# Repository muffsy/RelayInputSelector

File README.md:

# Muffsy Relay Input Selector 4

This open source (BSD license) project contains Arduino Code, Autodesk Eagle PCB project files and gerbers that can be sent directly to any PCB manufacturer for production.

- https://www.muffsy.com/muffsy-relay-input-selector-4.html
- https://www.tindie.com/products/skrodahl/muffsy-relay-input-selector-kit/

The Muffsy Relay Input Selector is a simple, reliable, high quality, DIY stereo input selector that's controlled by an ESP-32 and is slightly larger than a Post-IT note. 

The Input Selector has four inputs, one output, a mute circuit and the option of controlling a solid state relay. It's controlled with a rotary encoder and an IR remote. 

As the heart of the Input Selector is an ESP32, with all pins broken out on the board, the possibilities are virtually limitles. The example code is written in Arduino, the native SDK could of course be used instead.

This kit is meant to be paired with a preamplifier circuit, such as the Muffsy BSTRD Class-A Tube Preamp, Pass Labs B1 and many others.

**This project**, including the schematic and board layout, **is open source**. It's licensed under the very permissive BSD 3-Clause "New" or "Revised" License.

**Update 2023-07-30:**
The software now works without modifications of Arduino libraries.

**Update 2023-09-16:**
Much improved code, with user configurable values. In particular for the IR remote codes and rotary encoder direction.

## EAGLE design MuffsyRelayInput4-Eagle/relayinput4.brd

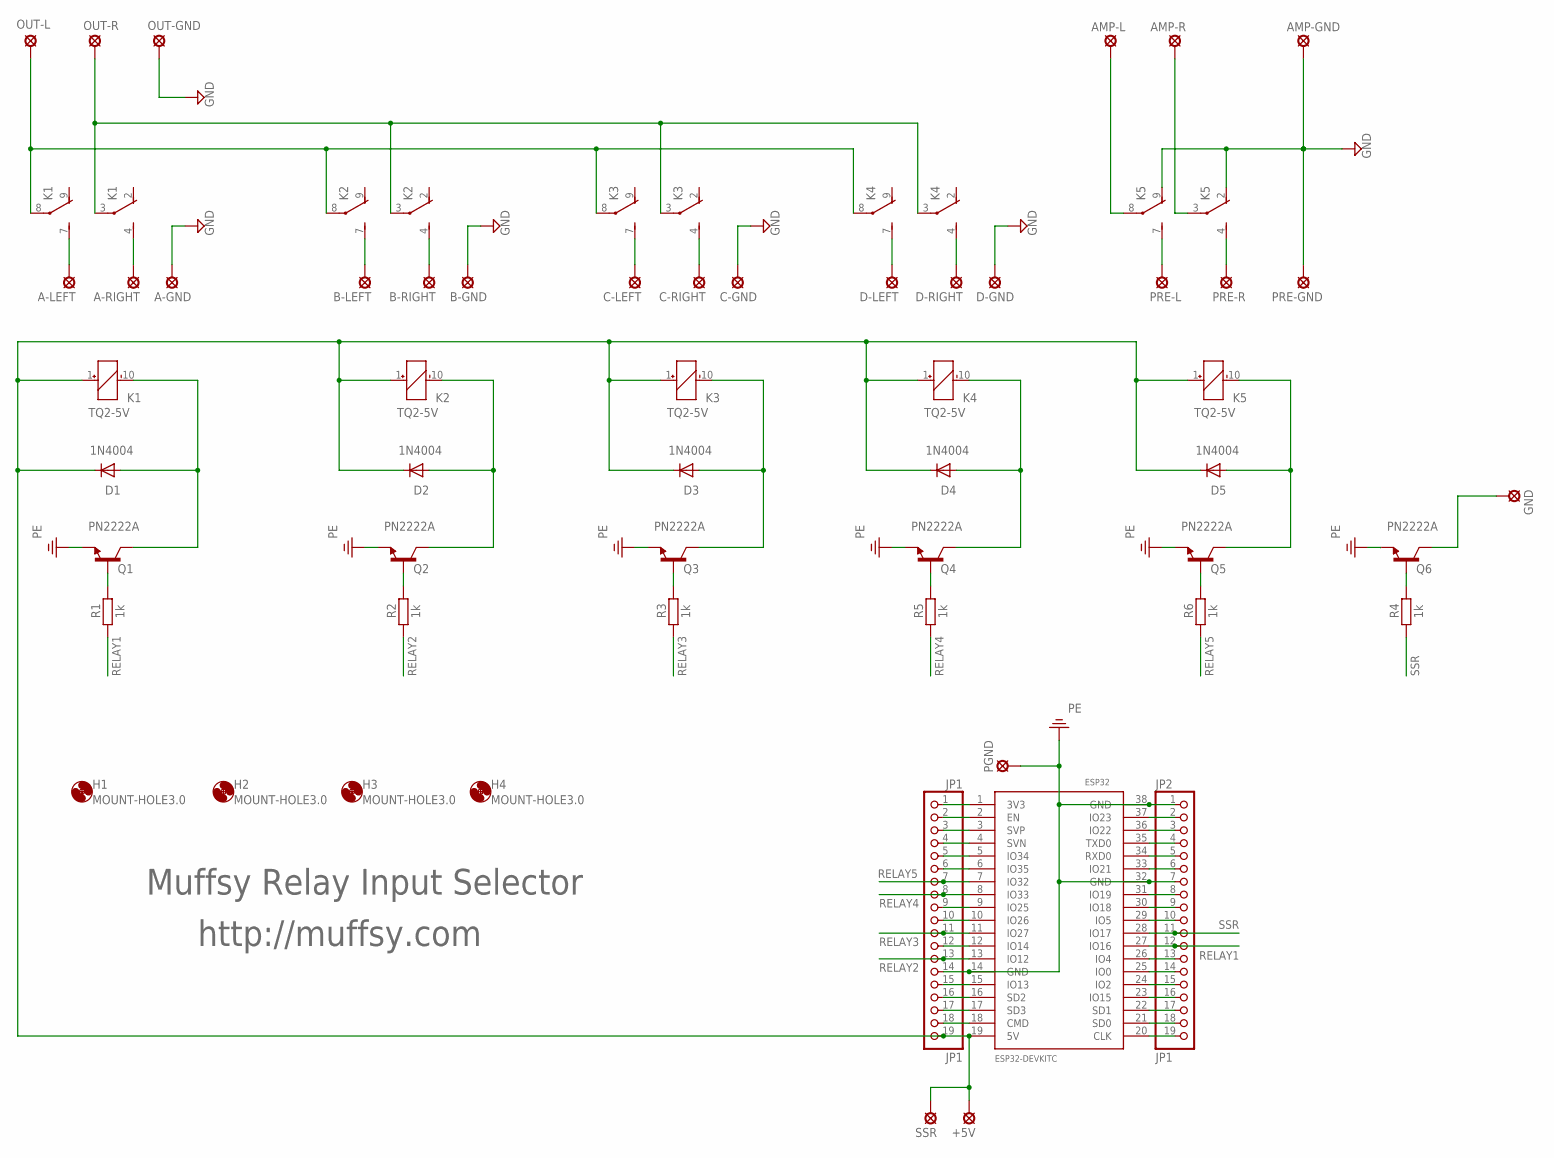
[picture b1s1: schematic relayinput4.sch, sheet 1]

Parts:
+5V: SE11
A-GND: SE11
A-LEFT: SE11
A-RIGHT: SE11
AMP-GND: SE11
AMP-L: SE11
AMP-R: SE11
B-GND: SE11
B-LEFT: SE11
B-RIGHT: SE11
C-GND: SE11
C-LEFT: SE11
C-RIGHT: SE11
D1, D2, D3, D4, D5: 1N4004; DO41-10
D-GND: SE11
D-LEFT: SE11
D-RIGHT: SE11
ESP32: ESP32DEVKITC; ESP32-DEVKITC
GND: SE11
H1, H2, H3, H4: MOUNT-HOLE3.0; 3,0
JP1, JP2: JP1; 1X19
K1, K2, K3, K4, K5: TQ2-5V; TQ2
OUT-GND: SE11
OUT-L: SE11
OUT-R: SE11
PGND: SE11
PRE-GND: SE11
PRE-L: SE11
PRE-R: SE11
Q1, Q2, Q3, Q4, Q5, Q6: PN2222A; TO92
R1, R2, R3, R4, R5, R6: 1k; 0207/10
SSR: SE11

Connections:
GND: A-GND.MP, AMP-GND.MP, B-GND.MP, C-GND.MP, D-GND.MP, K5.2 (O), K5.9 (O), OUT-GND.MP, PRE-GND.MP
unnamed: B-LEFT.MP, K2.7 (S)
unnamed: A-LEFT.MP, K1.7 (S)
unnamed: A-RIGHT.MP, K1.4 (S)
unnamed: B-RIGHT.MP, K2.4 (S)
unnamed: C-LEFT.MP, K3.7 (S)
unnamed: C-RIGHT.MP, K3.4 (S)
unnamed: D-LEFT.MP, K4.7 (S)
unnamed: D-RIGHT.MP, K4.4 (S)
unnamed: K5.7 (S), PRE-L.MP
unnamed: K5.4 (S), PRE-R.MP
unnamed: Q1.B, R1.2
unnamed: K1.3, K2.3, K3.3, K4.3, OUT-R.MP
unnamed: K1.8, K2.8, K3.8, K4.8, OUT-L.MP
unnamed: Q2.B, R2.2
unnamed: +5V.MP, D1.C, D2.C, D3.C, D4.C, D5.C, ESP32.19 (5V), JP1.19, K1.1 (+), K2.1 (+), K3.1 (+), K4.1 (+), K5.1 (+), SSR.MP
unnamed: Q3.B, R3.2
unnamed: Q4.B, R5.2
unnamed: Q5.B, R6.2
unnamed: ESP32.1 (3V3), JP1.1
unnamed: D1.A, K1.10 (-), Q1.C
unnamed: D2.A, K2.10 (-), Q2.C
unnamed: D3.A, K3.10 (-), Q3.C
unnamed: D4.A, K4.10 (-), Q4.C
unnamed: D5.A, K5.10 (-), Q5.C
unnamed: ESP32.2 (EN), JP1.2
unnamed: ESP32.3 (SVP), JP1.3
unnamed: ESP32.4 (SVN), JP1.4
unnamed: ESP32.5 (IO34), JP1.5
unnamed: ESP32.6 (IO35), JP1.6
unnamed: AMP-R.MP, K5.3
unnamed: AMP-L.MP, K5.8
unnamed: ESP32.10 (IO26), JP1.10
unnamed: ESP32.12 (IO14), JP1.12
unnamed: ESP32.9 (IO25), JP1.9
unnamed: GND.MP, Q6.C
unnamed: ESP32.15 (IO13), JP1.15
unnamed: Q6.B, R4.2
unnamed: ESP32.29 (IO5), JP2.10
unnamed: ESP32.36 (IO22), JP2.3
unnamed: ESP32.16 (SD2), JP1.16
unnamed: ESP32.17 (SD3), JP1.17
unnamed: ESP32.18 (CMD), JP1.18
unnamed: ESP32.37 (IO23), JP2.2
unnamed: ESP32.35 (TXD0), JP2.4
unnamed: ESP32.34 (RXD0), JP2.5
unnamed: ESP32.33 (IO21), JP2.6
unnamed: ESP32.31 (IO19), JP2.8
unnamed: ESP32.30 (IO18), JP2.9
unnamed: ESP32.26 (IO4), JP2.13
unnamed: ESP32.25 (IO0), JP2.14
unnamed: ESP32.24 (IO2), JP2.15
unnamed: ESP32.23 (IO15), JP2.16
unnamed: ESP32.22 (SD1), JP2.17
unnamed: ESP32.21 (SD0), JP2.18
unnamed: ESP32.20 (CLK), JP2.19
PE: ESP32.14 (GND), ESP32.32 (GND), ESP32.38 (GND), JP1.14, JP2.1, JP2.7, PGND.MP, Q1.E, Q2.E, Q3.E, Q4.E, Q5.E, Q6.E
RELAY1: ESP32.27 (IO16), JP2.12, R1.1
RELAY2: ESP32.13 (IO12), JP1.13, R2.1
RELAY3: ESP32.11 (IO27), JP1.11, R3.1
RELAY4: ESP32.8 (IO33), JP1.8, R5.1
RELAY5: ESP32.7 (IO32), JP1.7, R6.1
SSR: ESP32.28 (IO17), JP2.11, R4.1

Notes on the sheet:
Muffsy Relay Input Selector
http://muffsy.com

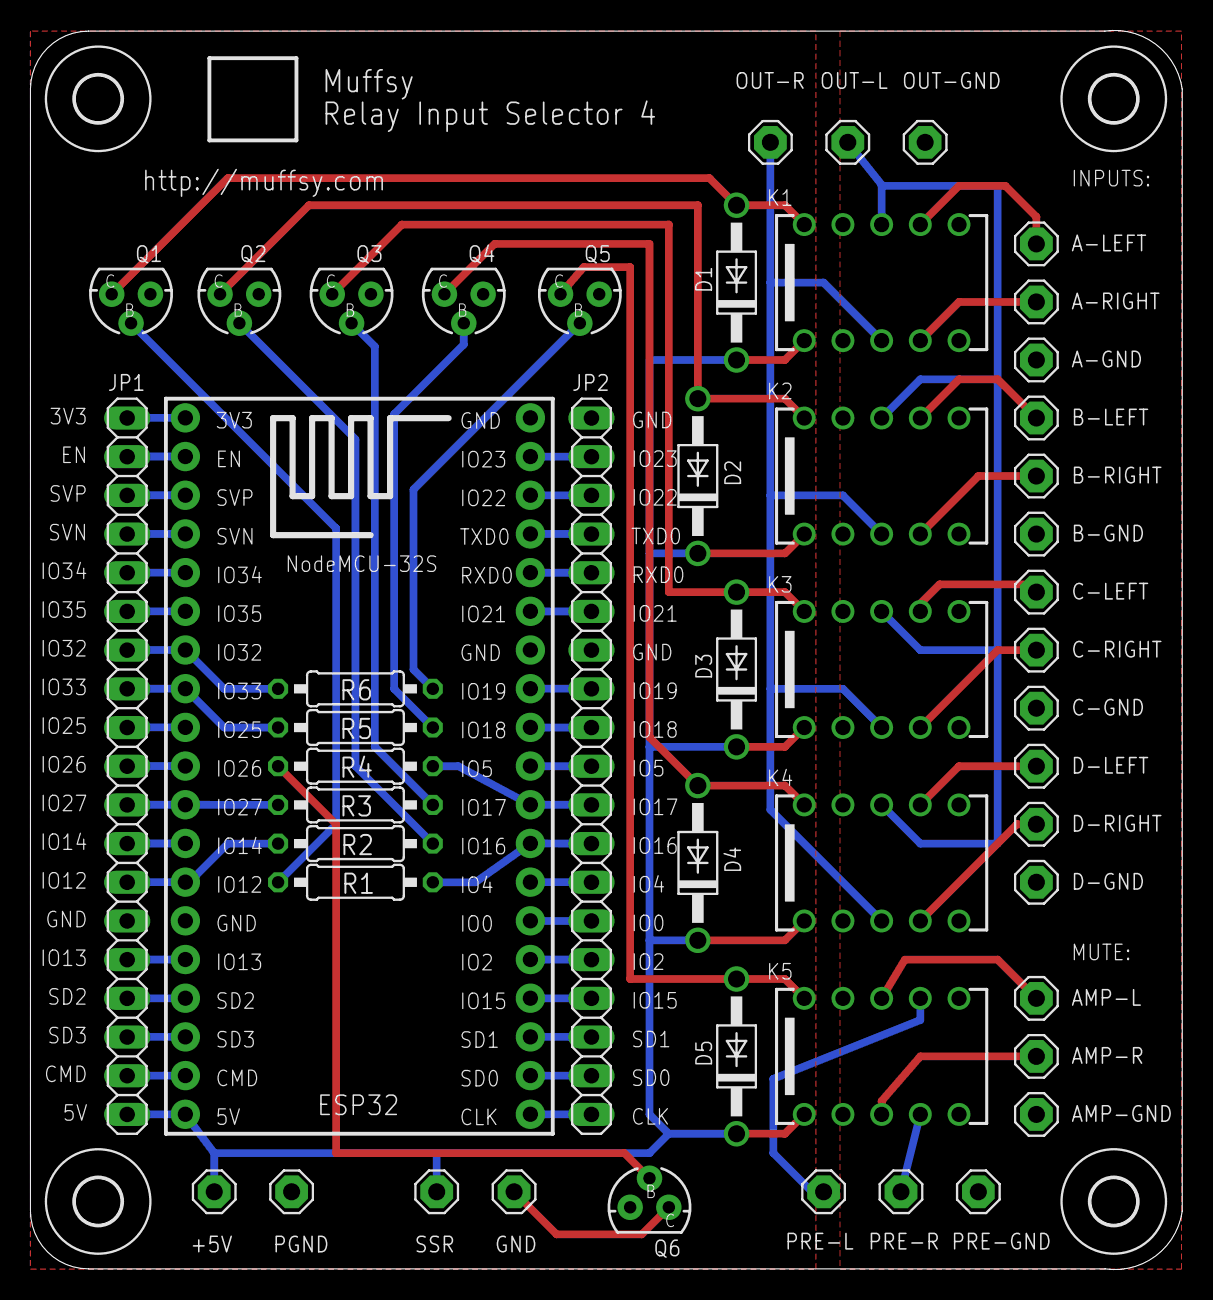
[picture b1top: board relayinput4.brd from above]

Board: 2 copper layers, 75.6 x 81.3 mm, 54 parts (0 on the bottom side), 63 nets.

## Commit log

2019-04-29 Added the IRremote.h library with fixes for ESP32
2019-04-29 Muffsy Relay Input Selector, Arduino code
    For the Muffsy Relay Input Selector 4:
    https://www.tindie.com/products/skrodahl/muffsy-relay-input-selector-kit/
2019-04-29 Added Eagle project files
    Included files: .sch, .brd, .cam, gerbers
2019-07-01 Update relayinput.ino
    Fixed mute.
    Was muted when it shouldn't, and vice versa.
2019-07-02 Update relayinput.ino
    Added muteLed
2019-07-04 Fixed problem with mute circuit
    Mute didn't ground the output (AMP-L/AMP-R), this version fixes that problem to make sure there's absolutely no hum while the circuit is turned off or muted.
2019-07-04 Eagle project files and gerbers
    Cosmetic changes to silkscreen top and bottom
2019-07-04 Eagle project files and gerbers
    More cosmetic changes, silkscreen top
2019-07-17 Update README.md
    Added more info on my patched IRremote.h library
2019-07-17 Update LICENSE
2019-07-18 Add files via upload
    Changed IR codes for the remote included in the kit
2020-01-16 Added PlatformIO Project
    The folder /MuffsyRelayInputSelector-PlatformIO is a fully self-contained PlatformIO project for the Muffsy Relay Input Selector. No more need for manual installation of the IRremote library.
2023-07-29 Delete IRremote directory
    No longer needed, EEPROM.h works without a patched version of IRRemote.h
2023-07-29 Delete relayinput.ino
    Adding MuffsyRelayInputSelector-Arduino.ino instead
2023-07-29 Add files via upload
    Updated file, patched libraries no longer needed
2023-07-29 Delete MuffsyRelayInputSelector-Arduino.ino
    Fix, file needs to be in a folder
2023-07-29 Add files via upload
    New version of the Arduino code, patched libraries no longer needed.
2023-07-31 Add files via upload
    Improved handling of rotary encoder, making variables volatile and atomic:
    https://forum.arduino.cc/t/esp32-crashes-when-turning-rotary-encoder-too-many-time-consecutively/1040123/2
2023-08-03 Update MuffsyRelayInputSelector-Arduino.ino
    Added timestamp
2023-09-16 Update MuffsyRelayInputSelector-Arduino.ino
    Cleaned up code, simplification and getting rid of duplicate/unnecessary code. Much improved comments. Using Versatile_Rotaryencoder.h for the rotary encoder instead of homegrown code. Added user con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
2023-09-16 Update MuffsyRelayInputSelector-Arduino.ino
    Fixed typo
2023-09-16 Update MuffsyRelayInputSelector-Arduino.ino
    Fixed startupDelay
2023-09-16 Update MuffsyRelayInputSelector-Arduino.ino
    FIX: muteLED was not turned off when input selector is powered off.
2023-09-16 Update MuffsyRelayInputSelector-Arduino.ino
    Updated instructions for startupDelay with how to disable the delay.
2023-09-16 Update MuffsyRelayInputSelector-Arduino.ino
    Added functionality for no delayed mute at power on.
2023-09-16 Update MuffsyRelayInputSelector-Arduino.ino
    FIX: Problem with rotary encoder if startupDelay set to other than 0.
2023-09-16 Update MuffsyRelayInputSelector-Arduino.ino
    Added clarifying comment
2023-09-16 Update MuffsyRelayInputSelector-Arduino.ino
    Small comment change
2023-09-16 Update MuffsyRelayInputSelector-Arduino.ino
    Added comment to the row that loads the rotary encoder library.
2023-09-16 Update MuffsyRelayInputSelector-Arduino.ino
    Updated comment for IR rate.
2023-09-17 Update MuffsyRelayInputSelector-Arduino.ino
    Updated default IR rate from 350 ms to 125 ms, as it gives a more natural behavior.
2023-09-17 Update MuffsyRelayInputSelector-Arduino.ino
    Changed the last updated day.
2023-09-17 Update MuffsyRelayInputSelector-Arduino.ino
    No change in functionality, updated comments on the IR commands with default values.
2023-09-17 Update MuffsyRelayInputSelector-Arduino.ino
    Added a user configurable option to slow down the turn rate of the rotary encoder. Default is no delay.
2023-09-17 Update MuffsyRelayInputSelector-Arduino.ino
    Cosmetic changes
2023-09-18 Update MuffsyRelayInputSelector-Arduino.ino
    Updated comment sections
2023-09-18 Update MuffsyRelayInputSelector-Arduino.ino
    Updated comments
2023-09-18 Update MuffsyRelayInputSelector-Arduino.ino
    Typo in comments
2023-09-18 Update MuffsyRelayInputSelector-Arduino.ino
    Preparing for user configurable setting "enableSSR"
2023-09-18 Update MuffsyRelayInputSelector-Arduino.ino
    Updated comment
2023-09-19 Update MuffsyRelayInputSelector-Arduino.ino
    Finished implementing user configurable option enableSSR. It is disabled by default, as mains power is dangerous. Also added better serial monitor output for the muteLed.
2023-09-19 Update MuffsyRelayInputSelector-Arduino.ino
    Bumped change date.
2023-09-19 Update MuffsyRelayInputSelector-Arduino.ino
    BUGFIX: If mute was on, changing the channel would turn it off. Fixed smaller bugs related to togglePower and added more comments.
2023-09-20 Update MuffsyRelayInputSelector-Arduino.ino
    Improved comments and formatting
2023-09-20 Update MuffsyRelayInputSelector-Arduino.ino
    Increased the IR Rate a smidge.
2023-09-27 Update MuffsyRelayInputSelector-Arduino.ino
    Added short delay after IR powerButton pressed, to avoid turning on immediately after power off.
2024-04-30 Delete MuffsyRelayInputSelector-PlatformIO directory
    Not maintained
2025-07-02 Create beta.ino
    First iteration
2025-07-02 Update beta.ino
    Web console
2026-05-19 autoPowerOn
    New user variable at line 62 — #define autoPowerOn 0 (set to 1 to enable), placed alongside the other startup-related defines like startupDelay and enableSSR.
    Hook into powerOn() at line 320 — after the welcome message finishes and powerState is set to 2, if autoPowerOn == 1 it calls togglePower() to power on.
    This preserves the full welcome/getting-ready flow (NVRAM read, mute relay, SSR off, startup message) and only then powers on — so the user-visible behavior is identical to a manual press, just witho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
